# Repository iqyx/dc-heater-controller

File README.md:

# 48 V heater controller

This aims to be a home-assistant compatible heater controller for off-grid water heating using
surplus electricity from a PV array. It is intended to be used in a 48 V DC system. Some main features:

- turn on the heating element whenever a surplus energy is detected
- cycle multiple heating elements to wear them evenly
- optimized for "3-phase" 48 V heating elements
- multiple redundant protections
- STM32 MCU with a ST's WiFi module for connectivity (no, no ESP32)
- water pump control

Implemented protections:

- high side MOSFET disconnect on UVLO (prevent draining the battery), can be set using a trimpot on the power board
- high side MOSFET disconnect on OV (well, not really important)
- high side MOSFET hardware overtemperature protection (turns them off)
- high side MOSFET software temperature monitoring
- high side current and voltage sense
- high side and low side MOSFETs software control depending on the battery voltage
- 95° water overtemperature hardware protection (a bimetal thermostat turns off high side MOSFETs)
- 90° water overtemperature hardware protection (a NTC with a comparator turns off low side MOSFETs independently of the software control)
- water temperature setpoint control (software controls low side MOSFETs)
- water pump malfunction turns off low side MOSFETs (software)

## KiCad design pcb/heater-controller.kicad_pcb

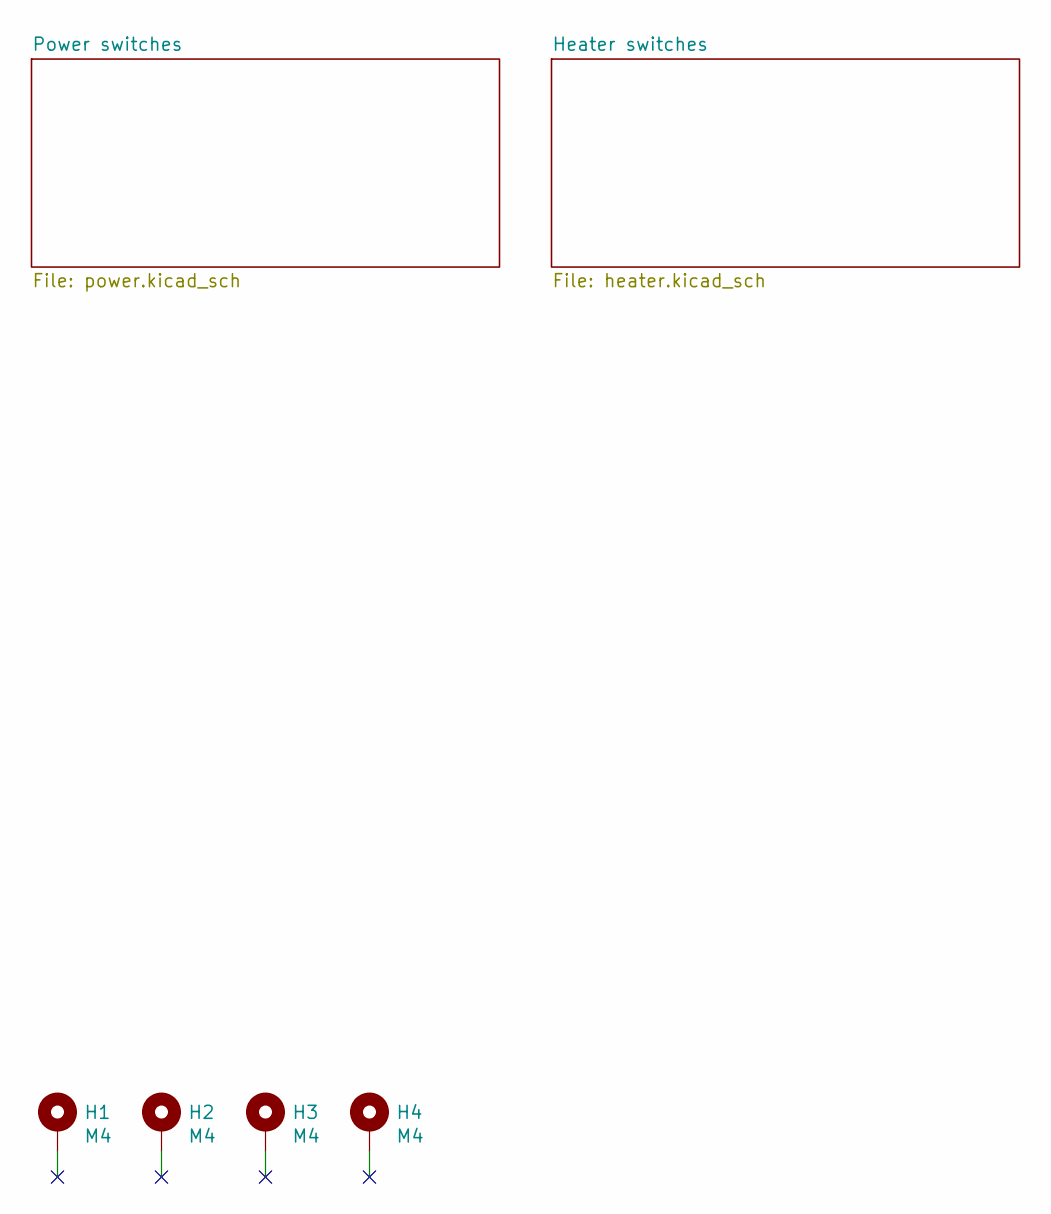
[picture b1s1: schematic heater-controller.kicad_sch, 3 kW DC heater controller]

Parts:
H1, H2, H3, H4: M4; MountingHole_4.3mm_M4_Pad_Via

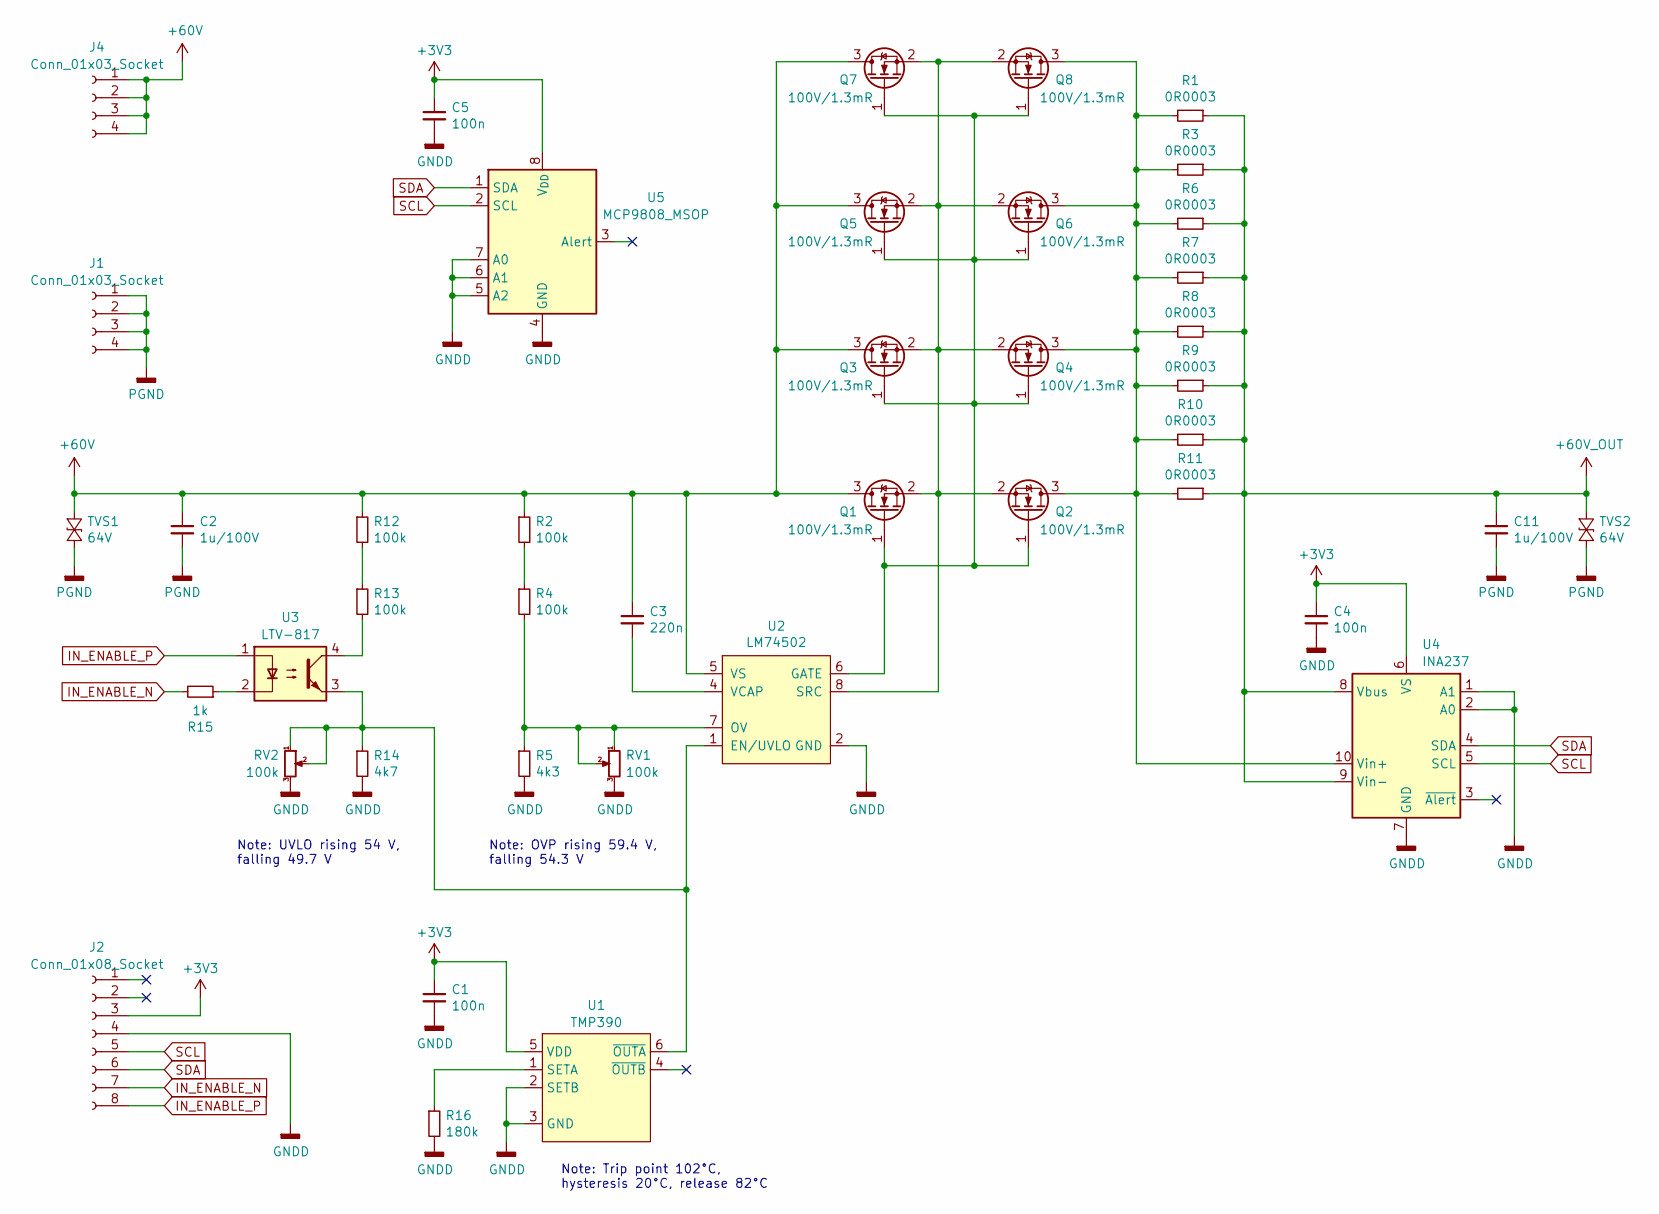
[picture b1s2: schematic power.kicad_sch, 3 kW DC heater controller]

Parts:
C1, C4, C5: 100n; C_0603_1608Metric
C2, C11: 1u/100V; C_1210_3225Metric
C3: 220n; C_0603_1608Metric
J1, J4: Conn_01x03_Socket; PinHeader_1x04_P2.54mm_Vertical
J2: Conn_01x08_Socket; PinHeader_1x08_P2.54mm_Vertical
Q1, Q2, Q3, Q4, Q5, Q6, Q7, Q8: 100V/1.3mR; Infineon_PG-HSOF-8-1
R1, R3, R6, R7, R8, R9, R10, R11: 0R0003; R_2512_6332Metric_Pad1.40x3.35mm_HandSolder
R2, R4, R12, R13: 100k; R_0603_1608Metric
R5: 4k3; R_0603_1608Metric
R14: 4k7; R_0603_1608Metric
R15: 1k; R_0603_1608Metric
R16: 180k; R_0603_1608Metric
RV1, RV2: 100k; Potentiometer_Bourns_3296Y_Vertical
TVS1, TVS2: 64V; D_SMC
U1: TMP390; SOT-666
U2: LM74502; SOT-23-8
U3: LTV-817; DIP-4_W7.62mm
U4: INA237; VSSOP-10_3x3mm_P0.5mm
U5: MCP9808_MSOP; MSOP-8_3x3mm_P0.65mm

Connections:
+3V3: C1.1, C4.1, C5.1, J2.3, U1.5 (VDD), U4.6 (VS), U5.8 (V_{DD})
+60V: C2.1, C3.1, J4.1, J4.2, J4.3, J4.4, Q1.3 (D), Q3.3 (D), Q5.3 (D), Q7.3 (D), R2.1, R12.1, TVS1.1 (K), U2.5 (VS)
+60V_OUT: C11.1, R1.1, R3.1, R6.1, R7.1, R8.1, R9.1, R10.1, R11.1, TVS2.1 (K), U4.8 (Vbus), U4.9 (Vin-)
GNDD: C1.2, C4.2, C5.2, J2.4, R5.2, R14.2, R16.2, RV1.3, RV2.3, U1.2 (SETB), U1.3 (GND), U2.2 (GND), U4.1 (A1), U4.2 (A0), U4.7 (GND), U5.4 (GND), U5.5 (A2), U5.6 (A1), U5.7 (A0)
IN_ENABLE_N: J2.7, R15.2
IN_ENABLE_P: J2.8, U3.1
unnamed: Q1.1 (G), Q2.1 (G), Q3.1 (G), Q4.1 (G), Q5.1 (G), Q6.1 (G), Q7.1 (G), Q8.1 (G), U2.6 (GATE)
unnamed: Q1.2 (S), Q2.2 (S), Q3.2 (S), Q4.2 (S), Q5.2 (S), Q6.2 (S), Q7.2 (S), Q8.2 (S), U2.8 (SRC)
unnamed: Q2.3 (D), Q4.3 (D), Q6.3 (D), Q8.3 (D), R1.2, R3.2, R6.2, R7.2, R8.2, R9.2, R10.2, R11.2, U4.10 (Vin+)
unnamed: R2.2, R4.1
unnamed: R12.2, R13.1
unnamed: R13.2, U3.4
unnamed: R15.1, U3.2
unnamed: R16.1, U1.1 (SETA)
unnamed: R14.1, RV2.1, RV2.2, U1.6 (~OUTA), U2.1 (EN/UVLO), U3.3
unnamed: R4.2, R5.1, RV1.1, RV1.2, U2.7 (OV)
unnamed: C3.2, U2.4 (VCAP)
PGND: C2.2, C11.2, J1.1, J1.2, J1.3, J1.4, TVS1.2 (A), TVS2.2 (A); also elsewhere on the board
SCL: J2.5, U4.5 (SCL), U5.2 (SCL)
SDA: J2.6, U4.4 (SDA), U5.1 (SDA)

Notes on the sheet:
Note: Trip point 102°C, hysteresis 20°C, release 82°C
Note: OVP rising 59.4 V, falling 54.3 V
Note: UVLO rising 54 V, falling 49.7 V

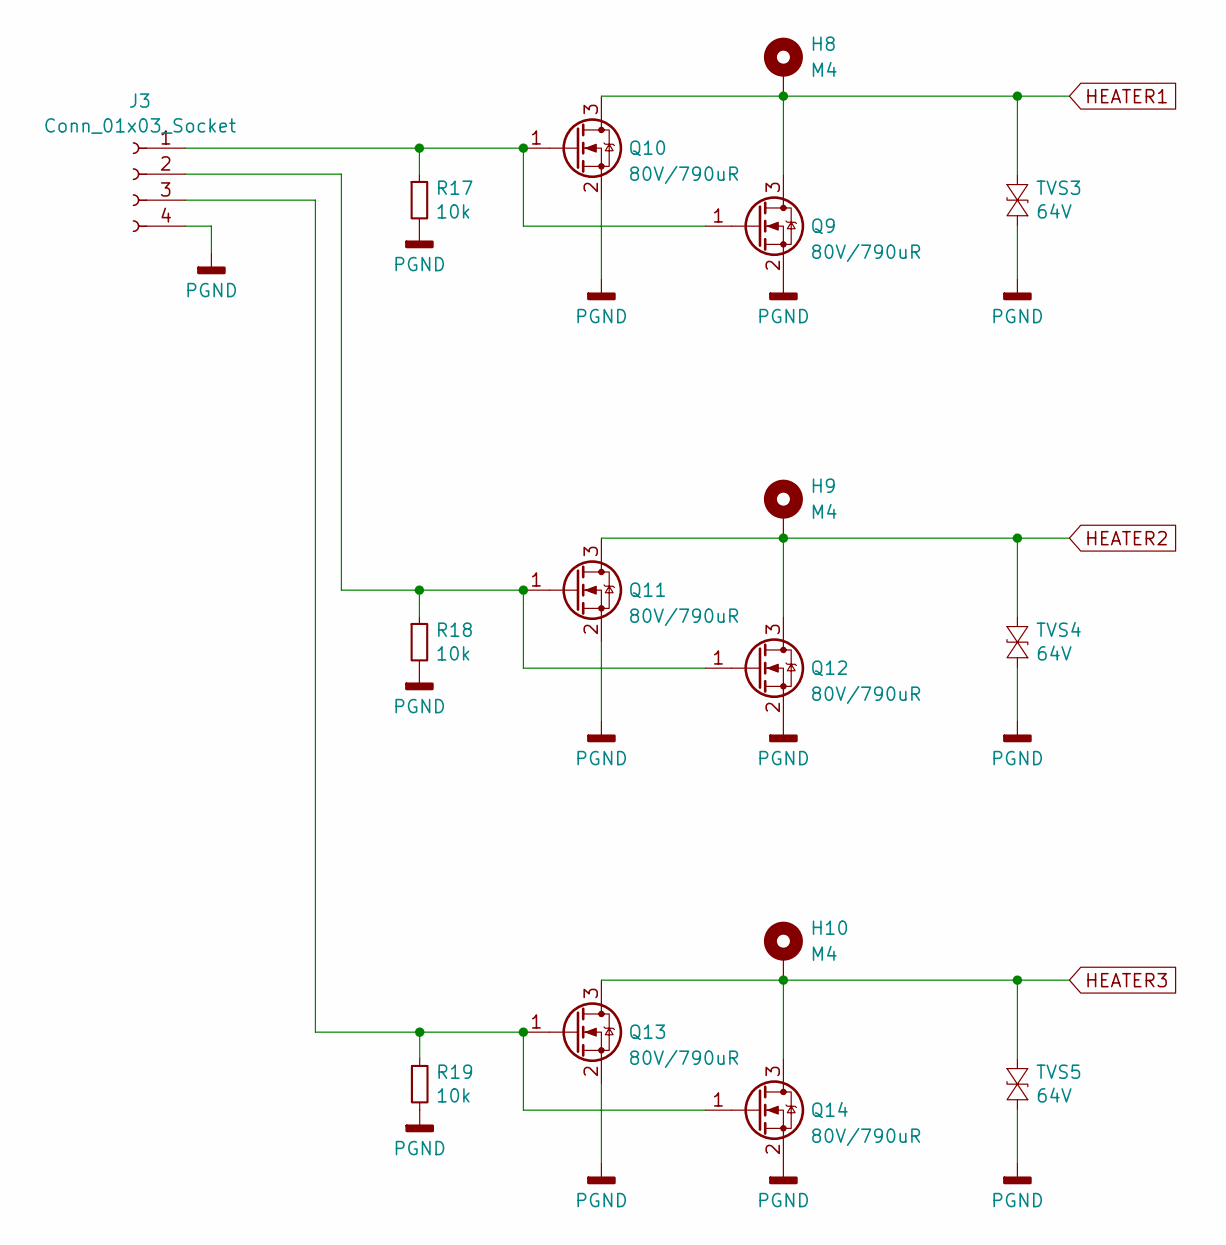
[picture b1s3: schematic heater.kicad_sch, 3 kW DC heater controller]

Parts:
H8, H9, H10: M4; KEYS_7798
J3: Conn_01x03_Socket; PinHeader_1x04_P2.54mm_Vertical
Q9, Q10, Q11, Q12, Q13, Q14: 80V/790uR; Infineon_PG-HSOF-8-1
R17, R18, R19: 10k; R_0603_1608Metric
TVS3, TVS4, TVS5: 64V; D_SMC

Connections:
HEATER1: H8.1, Q9.3 (D), Q10.3 (D), TVS3.1 (K)
HEATER2: H9.1, Q11.3 (D), Q12.3 (D), TVS4.1 (K)
HEATER3: H10.1, Q13.3 (D), Q14.3 (D), TVS5.1 (K)
unnamed: J3.1, Q9.1 (G), Q10.1 (G), R17.1
unnamed: J3.2, Q11.1 (G), Q12.1 (G), R18.1
unnamed: J3.3, Q13.1 (G), Q14.1 (G), R19.1
PGND: J3.4, Q9.2 (S), Q10.2 (S), Q11.2 (S), Q12.2 (S), Q13.2 (S), Q14.2 (S), R17.2, R18.2, R19.2, TVS3.2 (A), TVS4.2 (A), TVS5.2 (A); also elsewhere on the board

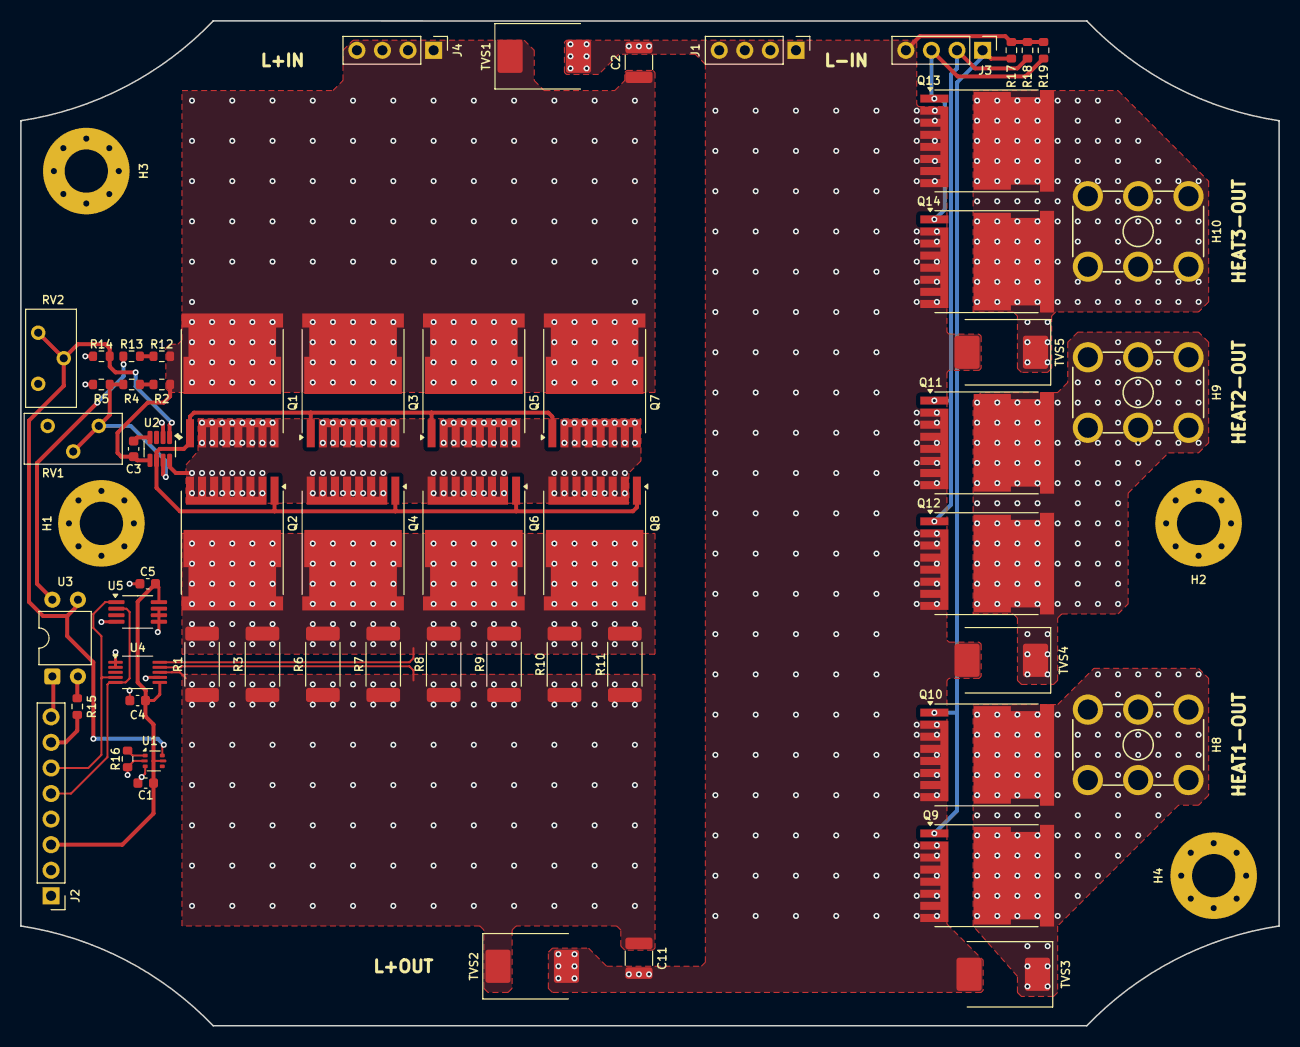
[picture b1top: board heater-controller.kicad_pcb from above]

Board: 2 copper layers, 125.0 x 99.8 mm, 62 parts (0 on the bottom side), 26 nets.

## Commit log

2026-01-06 Update sch & pcb
2026-01-06 chore: Add gerber output

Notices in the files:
pcb/heater-controller.kicad_sch:
(c) 2024, Marek Koza
